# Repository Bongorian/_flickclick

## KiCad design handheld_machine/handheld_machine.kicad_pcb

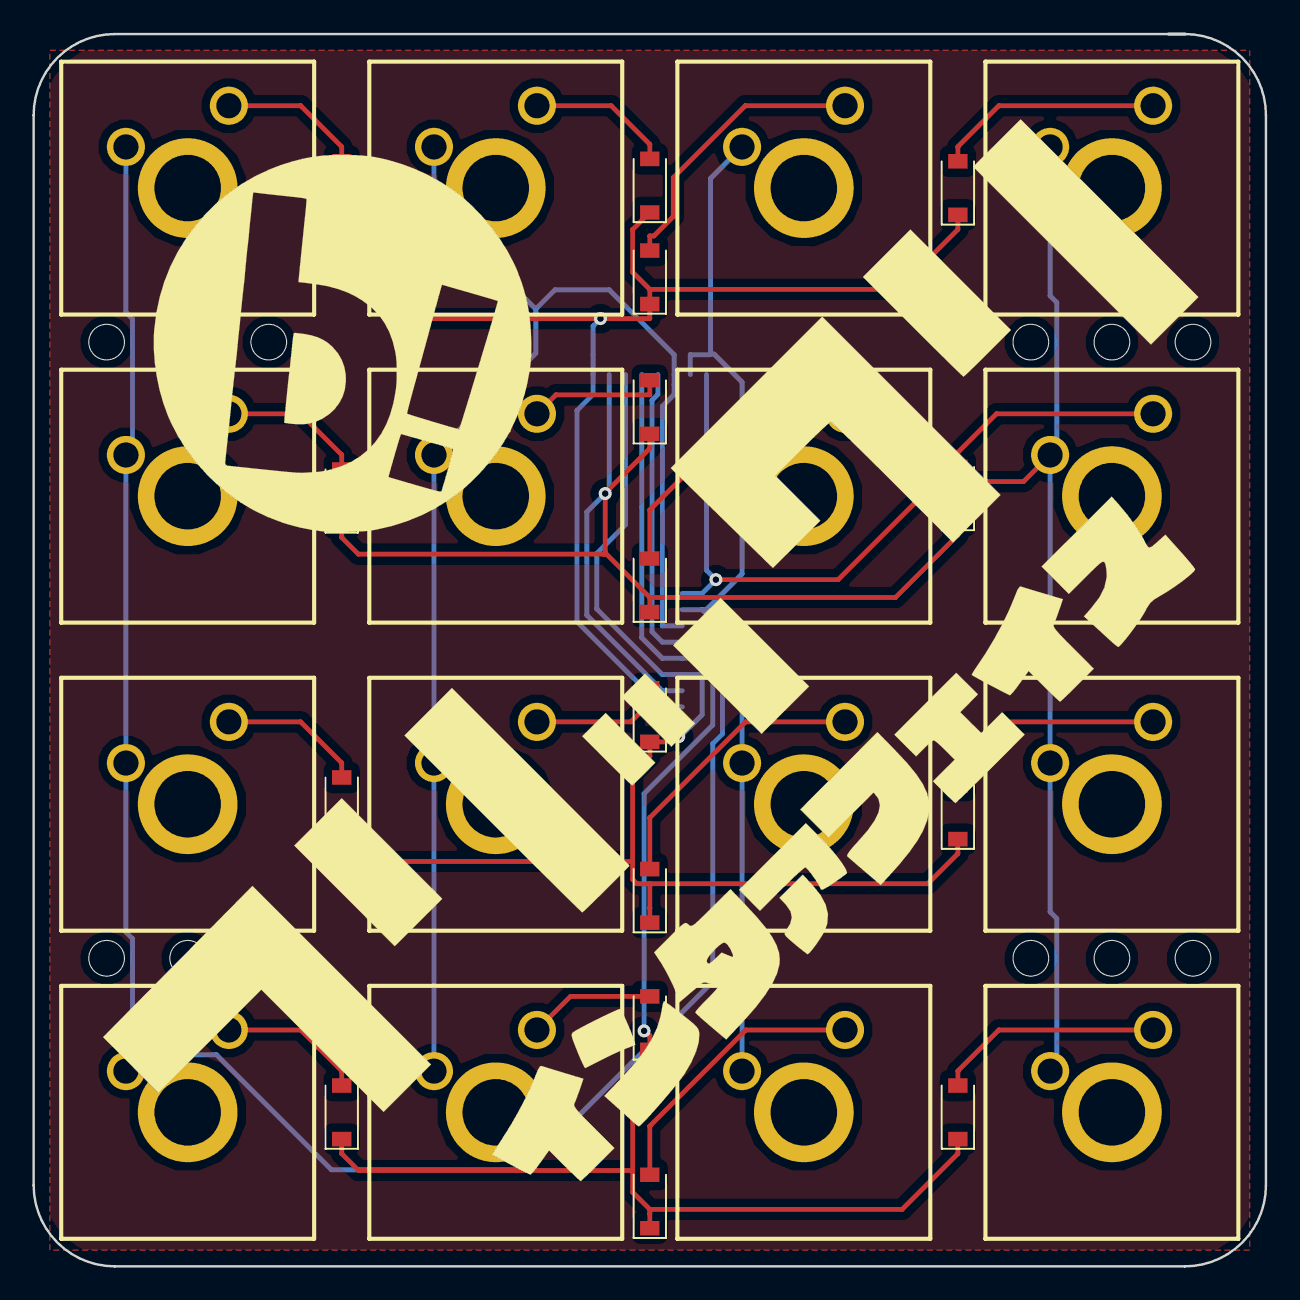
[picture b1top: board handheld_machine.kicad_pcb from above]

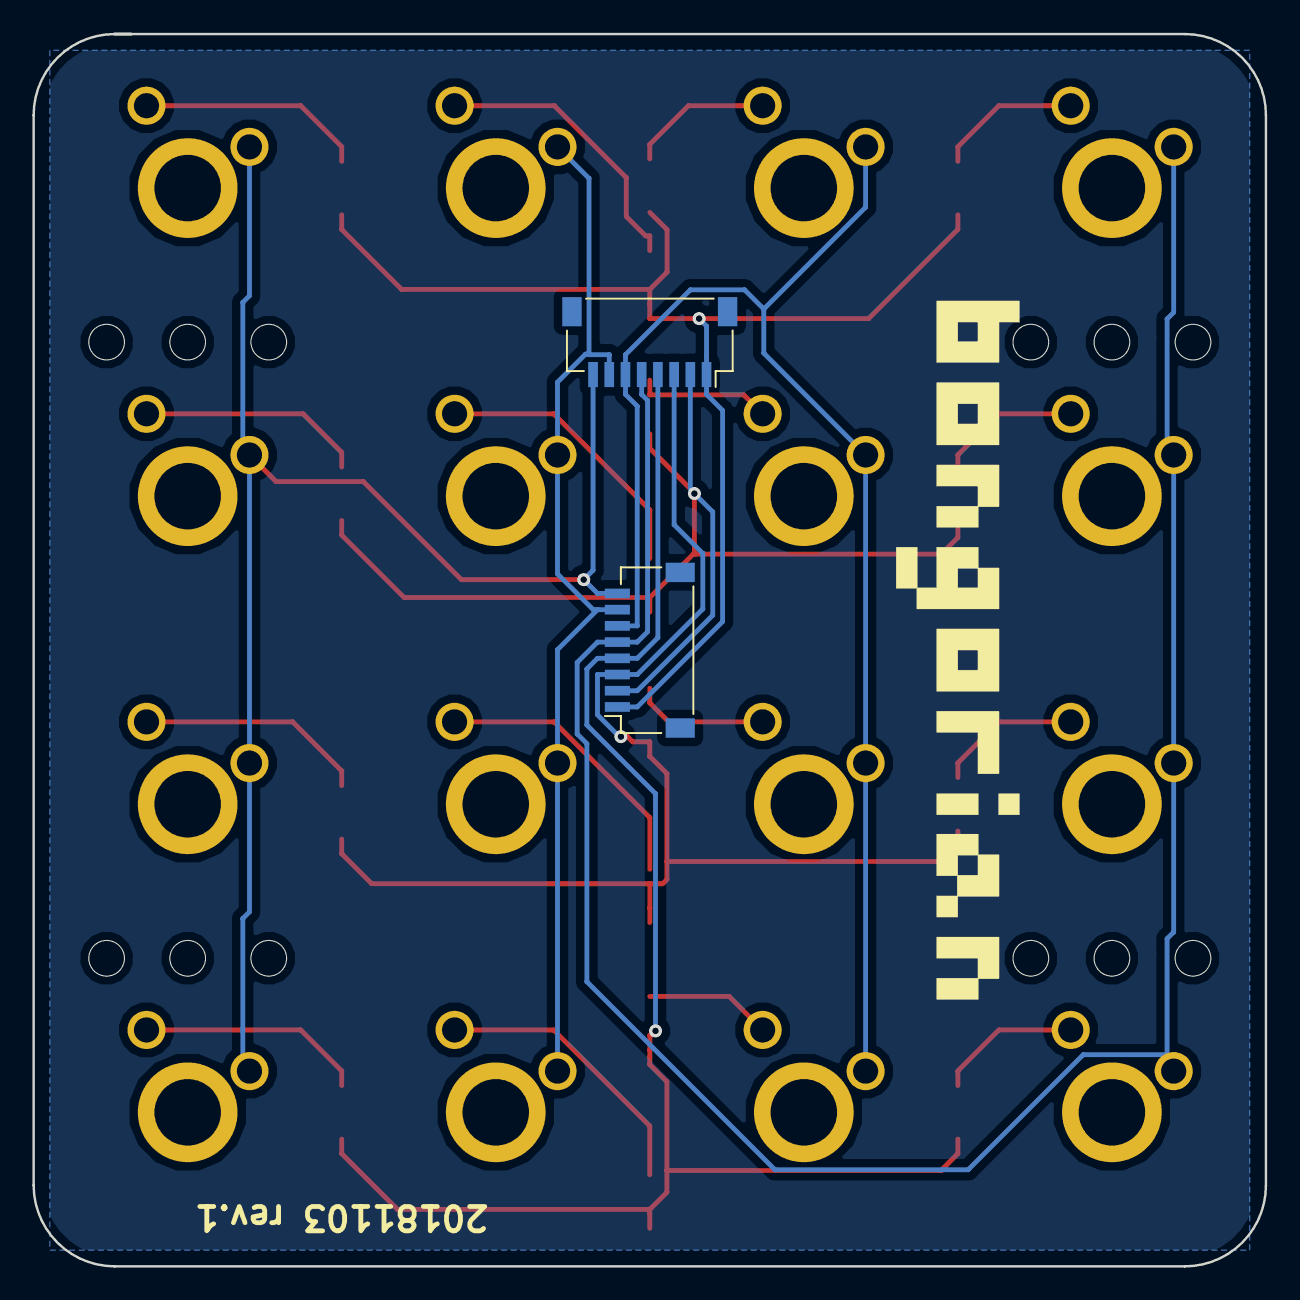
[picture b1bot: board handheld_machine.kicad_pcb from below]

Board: 2 copper layers, 76.0 x 76.0 mm, 49 parts (3 on the bottom side), 24 nets.

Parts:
D1, D2, D3, D4, D5, D6, D7, D8, D9, D10, D11, D12, D13, D14, D15, D16: D; D_SOD-123
G1: flcl_logo
G2: bongorian
G3: flcl_pakuri
J1, J2: Conn_01x08_Female; JST_SH_SM08B-SRSS-TB_1x08-1MP_P1.00mm_Horizontal
SW1, SW2, SW3, SW4, SW5, SW6, SW7, SW8, SW9, SW10, SW11, SW12, SW13, SW14, SW15, SW16: SW_Push; cherry
h1, h2, h3, h4, h11, h13, h21, h23, h31, h33, h41, h43: MountingHole_2.2mm_M2

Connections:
unnamed: D1.2, SW1.2
unnamed: D2.2, SW2.2
unnamed: D3.2, SW3.2
unnamed: D4.2, SW4.2
unnamed: D5.2, SW5.2
unnamed: D6.2, SW6.2
unnamed: D7.2, SW7.2
unnamed: D8.2, SW8.2
unnamed: D9.2, SW9.2
unnamed: D10.2, SW10.2
unnamed: D11.2, SW11.2
unnamed: D12.2, SW12.2
unnamed: D13.2, SW13.2
unnamed: D14.2, SW14.2
unnamed: D15.2, SW15.2
unnamed: D16.2, SW16.2
col1: J1.5, J2.5, SW1.1, SW5.1, SW9.1, SW13.1
col2: J1.6, J2.6, SW2.1, SW6.1, SW10.1, SW14.1
col3: J1.7, J2.7, SW3.1, SW7.1, SW11.1, SW15.1
col4: J1.8, J2.8, SW4.1, SW8.1, SW12.1, SW16.1
row1: D1.1, D2.1, D3.1, D4.1, J1.1, J2.1
row2: D5.1, D6.1, D7.1, D8.1, J1.2, J2.2
row3: D9.1, D10.1, D11.1, D12.1, J1.3, J2.3
row4: D13.1, D14.1, D15.1, D16.1, J1.4, J2.4

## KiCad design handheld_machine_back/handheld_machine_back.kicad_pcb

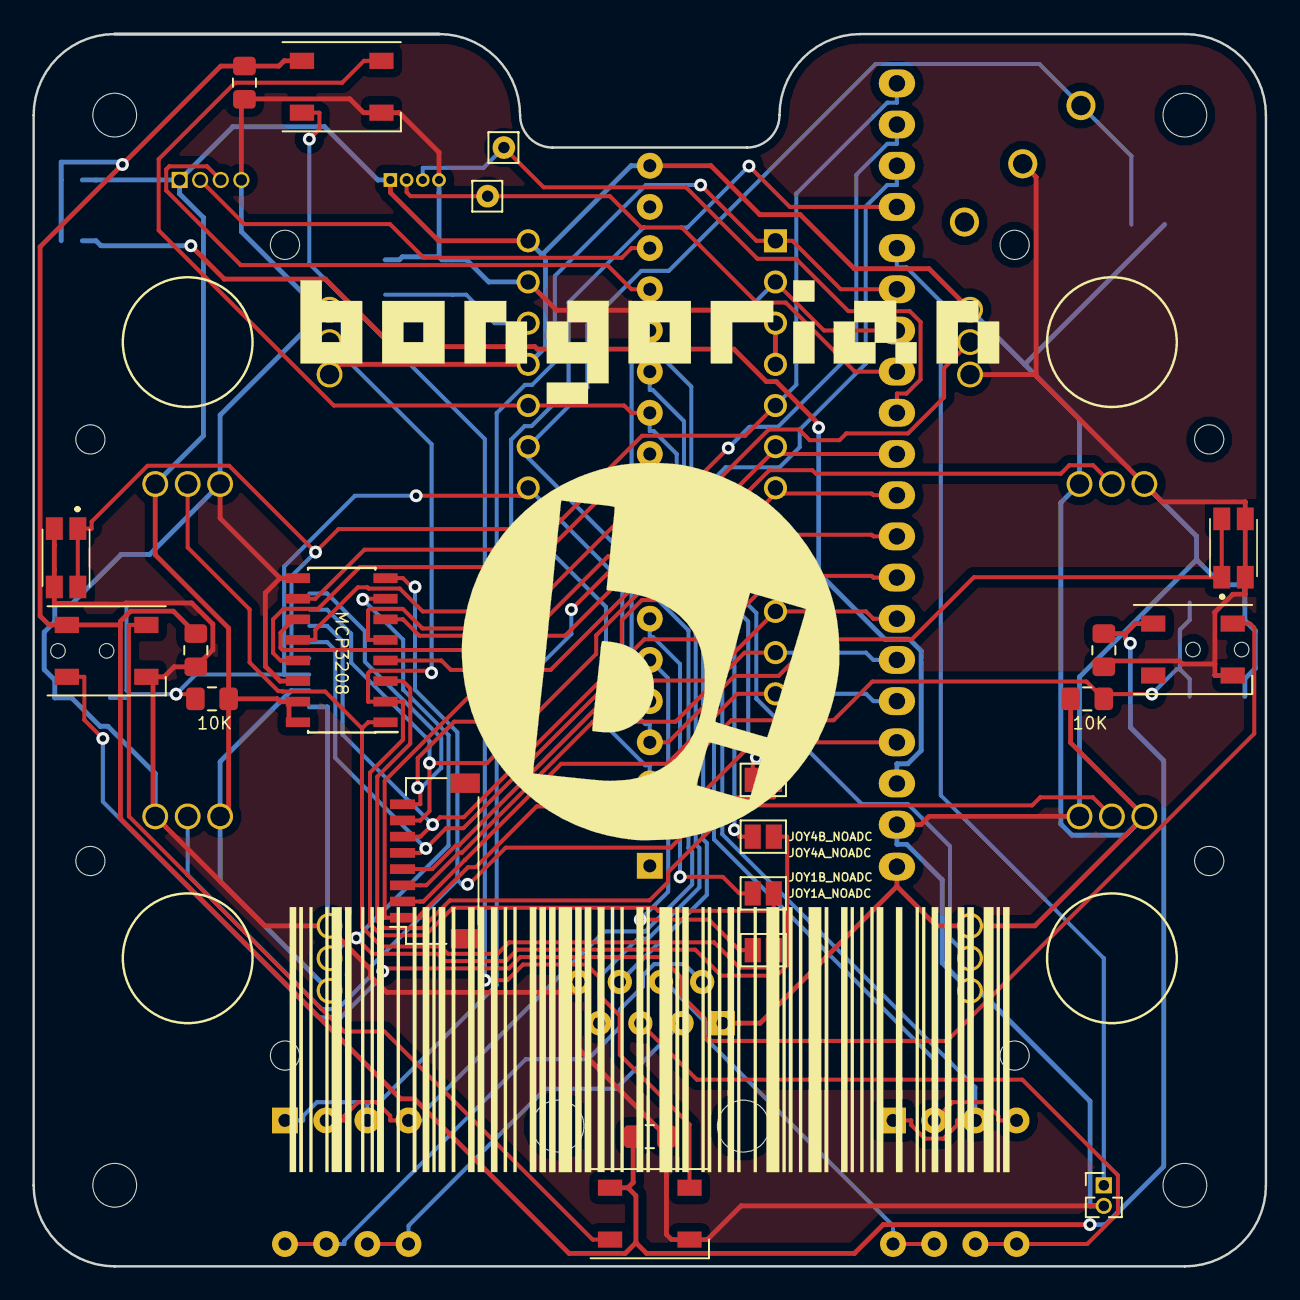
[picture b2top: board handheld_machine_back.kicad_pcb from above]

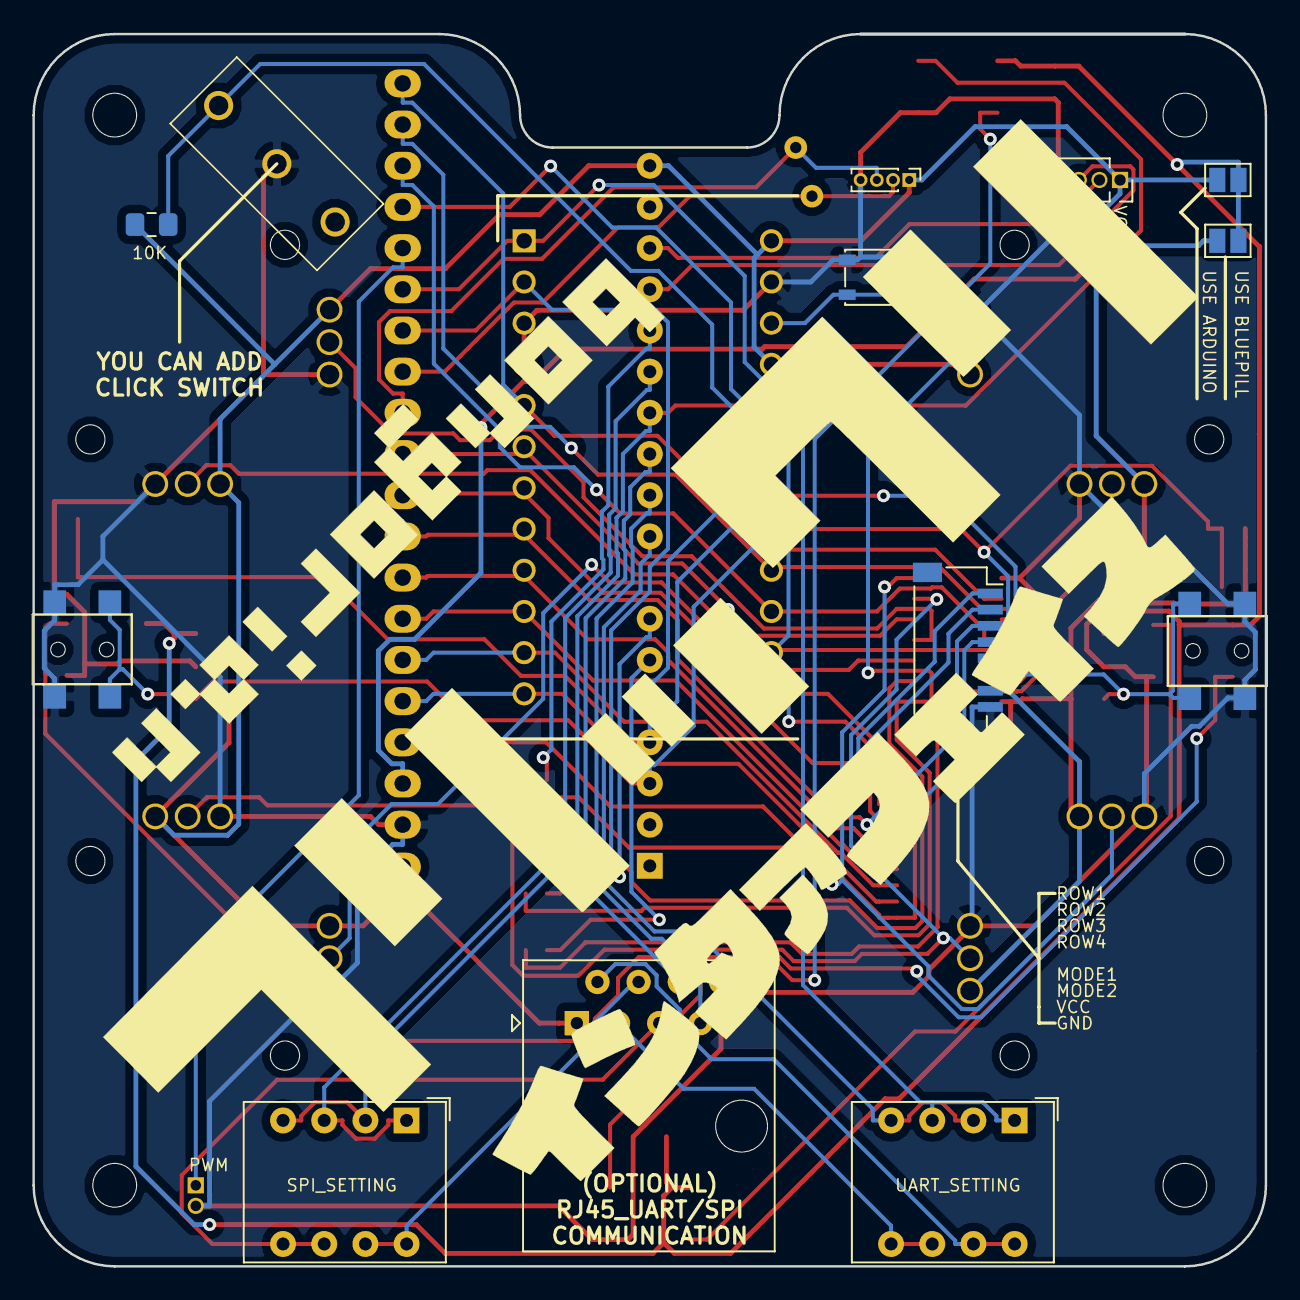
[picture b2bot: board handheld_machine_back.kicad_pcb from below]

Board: 2 copper layers, 76.0 x 76.0 mm, 44 parts (15 on the bottom side), 50 nets.

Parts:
C1, C2, C3, C4: C; C_0805_2012Metric_Pad1.15x1.40mm_HandSolder
D1, D2, D3, D4: WS2812B; LED_WS2812B_PLCC4_5.0x5.0mm_P3.2mm
IC1: Pro Micro; DIPS1525W55P254L3325H1250Q24N
J1: Conn_01x04_Male; PinHeader_1x04_P1.00mm_Vertical
J2: from_front; JST_SH_SM08B-SRSS-TB_1x08-1MP_P1.00mm_Horizontal
J3: to_back; JST_SH_SM08B-SRSS-TB_1x08-1MP_P1.00mm_Horizontal
J4: Conn_01x08_Female; RJ45_Amphenol_54602-x08_Horizontal
J5: Conn_01x04_Male; PinSocket_1x04_P1.27mm_Vertical
J6: Conn_01x02_Male; PinHeader_1x02_P1.27mm_Vertical
JP1: ARDUINO; SolderJumper-2_P1.3mm_Open_Pad1.0x1.5mm
JP2: BLUEPILL; SolderJumper-2_P1.3mm_Open_Pad1.0x1.5mm
JP3, JP4, JP5, JP6: Jumper_NO_Small; SolderJumper-2_P1.3mm_Open_Pad1.0x1.5mm
MH1, MH2, MH3, MH4: MountingHole; MountingHole_2.7mm_M2.5
R1, R2, R3: 10k; R_0805_2012Metric_Pad1.15x1.40mm_HandSolder
S1, S2: EVQ-P7J01P; EVQP7J01P
SW1: firmware_sw; SW_SPST_PTS810
SW2: mode1; horizonal_tact
SW3: mode2; horizonal_tact
SW4: ENTER; D2FT
SW5, SW6: SW_DIP_x04; SW_DIP_SPSTx04_Slide_9.78x12.34mm_W7.62mm_P2.54mm
TP1, TP2: TestPoint; Pin_D0.7mm_L6.5mm_W1.8mm_FlatFork
U1, U2, U3, U4: joystick_thin
U5: MCP3208; SOIC-16_3.9x9.9mm_P1.27mm
U6: BluePill_STM32F103C; noashi_bluepill2

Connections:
CLK: IC1.16, U5.13, U6.22
CS: IC1.5, U5.10, U6.21
DIN: IC1.14, U5.11, U6.24
DOUT: IC1.15, U5.12, U6.23
GND: C1.2, C2.2, C3.2, C4.2, D1.3, D2.3, D3.3, D4.3, IC1.3, IC1.4, IC1.23, J1.4, J3.8, J4.8, J5.4, J6.2, S1.3, S1.4, S2.3, S2.4, SW1.2, SW2.2, SW2.4, SW3.2, SW3.4, SW4.2, U1.1, U1.4, U2.1, U2.4, U3.1, U3.4, U4.1, U4.4, U5.9, U5.14, U6.39
JOY1A: JP6.2, U1.2, U5.1
JOY1B: JP5.2, U1.5, U5.2
JOY2A: U3.2, U5.3
JOY2B: U3.5, U5.4
JOY3A: U2.2, U5.5
JOY3B: U2.5, U5.6
JOY4A: JP4.2, U4.2, U5.7
JOY4B: JP3.2, U4.5, U5.8
LED_D1: D1.4, IC1.20, SW6.1, SW6.3, U6.12
MISO1: SW6.2, SW6.4, U6.11
unnamed: C1.1, C2.1, C3.1, C4.1, D1.1, D2.1, D3.1, D4.1, JP1.2, JP2.2
unnamed: D1.2, D2.4
unnamed: D2.2, D3.4
unnamed: D3.2, D4.4
unnamed: IC1.22, SW1.1
unnamed: JP3.1, U6.14
unnamed: JP4.1, U6.13
unnamed: JP5.1, U6.7
unnamed: JP6.1, U6.6
PROMICRO_D+: J1.3, TP1.1, U6.29
PROMICRO_D-: J1.2, TP2.1, U6.28
RX: IC1.2, SW5.2, SW5.4, U6.27
SCK1: J4.6, U6.10
SCL: J5.3, U6.15
SDA: J5.2, U6.16
SS1: J4.7, U6.9
TX: IC1.1, SW5.1, SW5.3, U6.26
USBVCC: JP2.1, U6.38
VCC: IC1.21, IC1.24, J1.1, J3.7, J4.1, J5.1, JP1.1, R1.1, R2.1, R3.1, U1.3, U1.6, U2.3, U2.6, U3.3, U3.6, U4.3, U4.6, U5.15, U5.16, U6.18, U6.40
col1: IC1.10, J2.4, U6.34
col2: IC1.11, J2.3, U6.35
col3: IC1.12, J2.2, U6.36
col4: IC1.13, J2.1, U6.37
enter: IC1.19, R3.2, SW4.1, U6.5
mode1: IC1.17, J3.5, R1.2, S1.1, S1.2, SW2.1, SW2.3, U6.3
mode2: IC1.18, J3.6, R2.2, S2.1, S2.2, SW3.1, SW3.3, U6.4
pin2: J4.2, SW5.7, SW5.8
pin3: J4.3, SW5.5, SW5.6
pin4: J4.4, SW6.7, SW6.8
pin5: J4.5, SW6.5, SW6.6
pwm1: J6.1, U6.25
row1: IC1.6, J2.8, J3.1, U6.30
row2: IC1.7, J2.7, J3.2, U6.31
row3: IC1.8, J2.6, J3.3, U6.32
row4: IC1.9, J2.5, J3.4, U6.33

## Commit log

2018-11-06 init
